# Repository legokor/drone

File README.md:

This repository houses all the essential project files for the drone project. It encompasses schematics, PCB designs, and firmwares.

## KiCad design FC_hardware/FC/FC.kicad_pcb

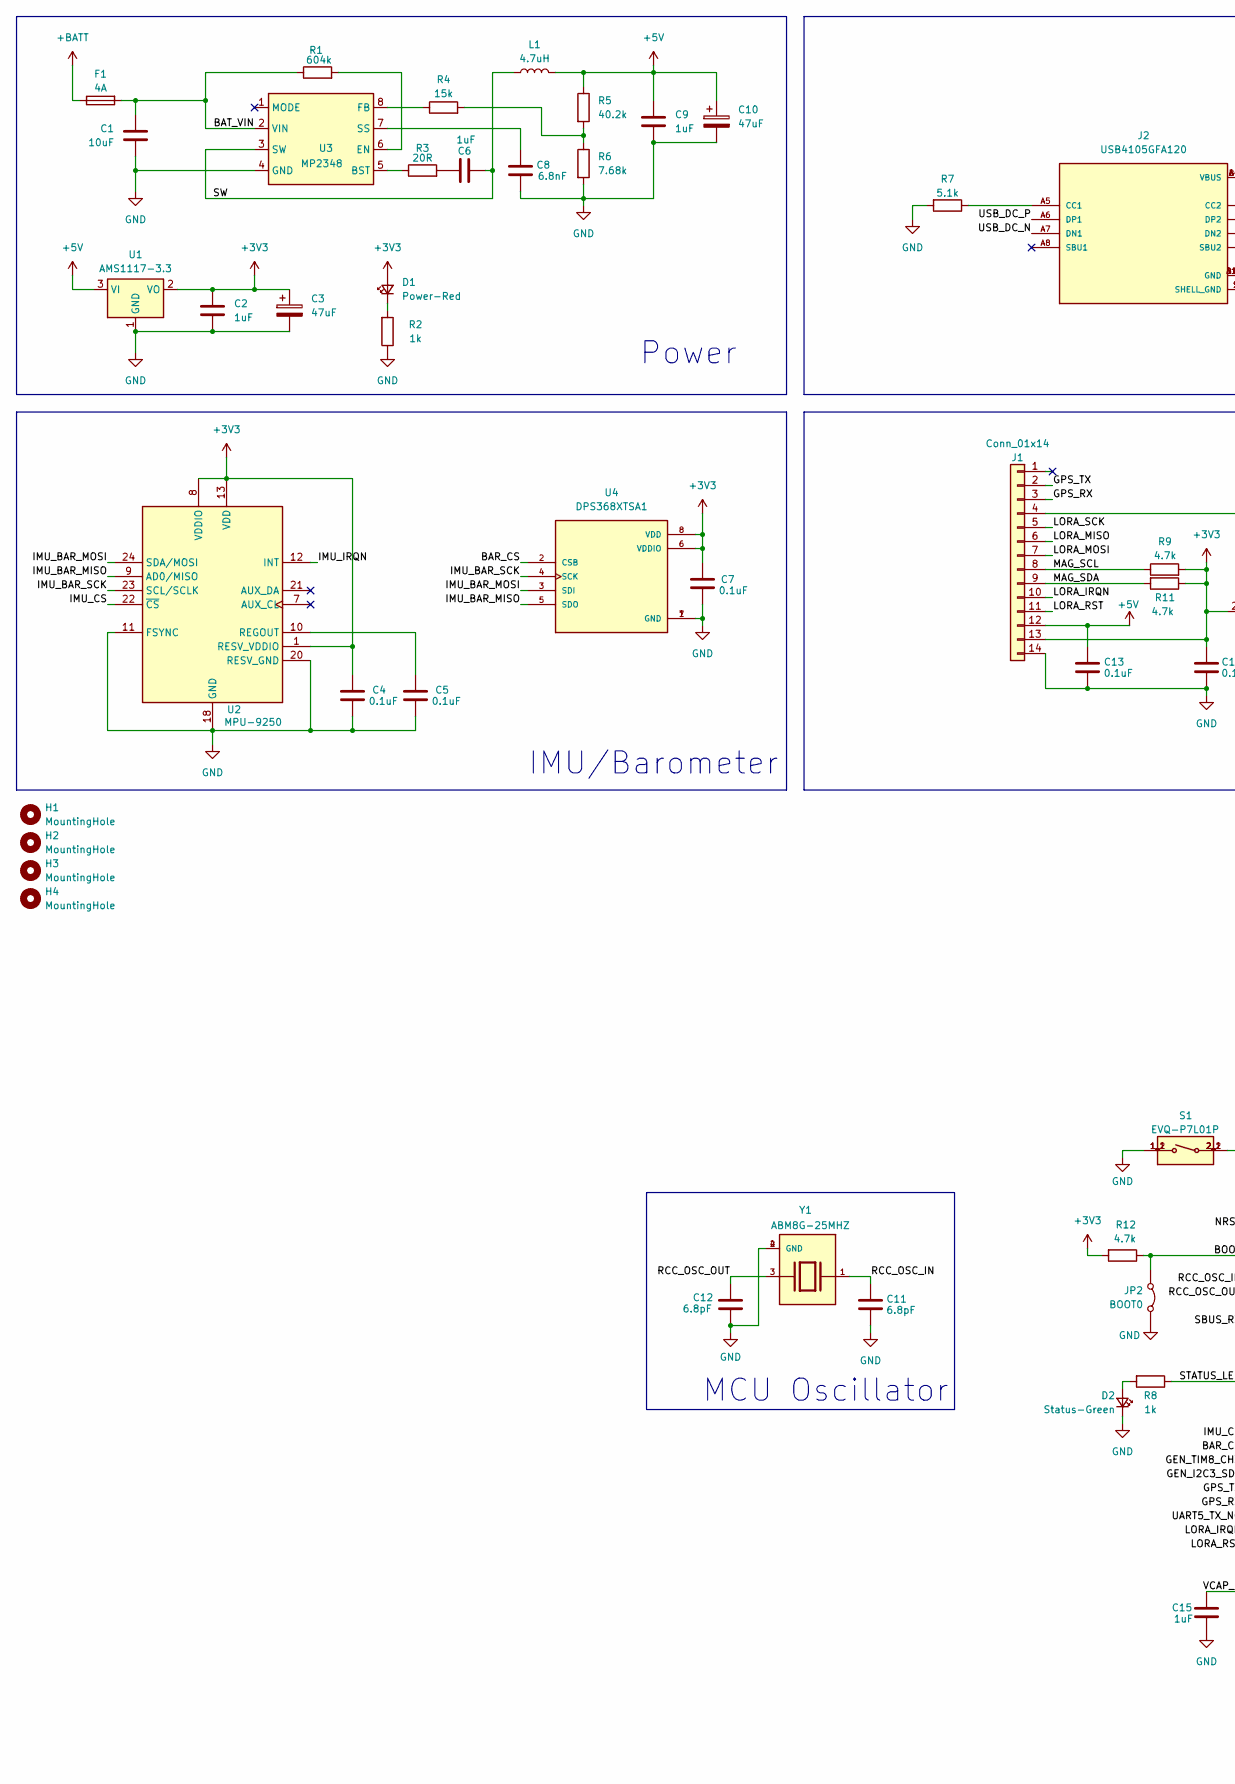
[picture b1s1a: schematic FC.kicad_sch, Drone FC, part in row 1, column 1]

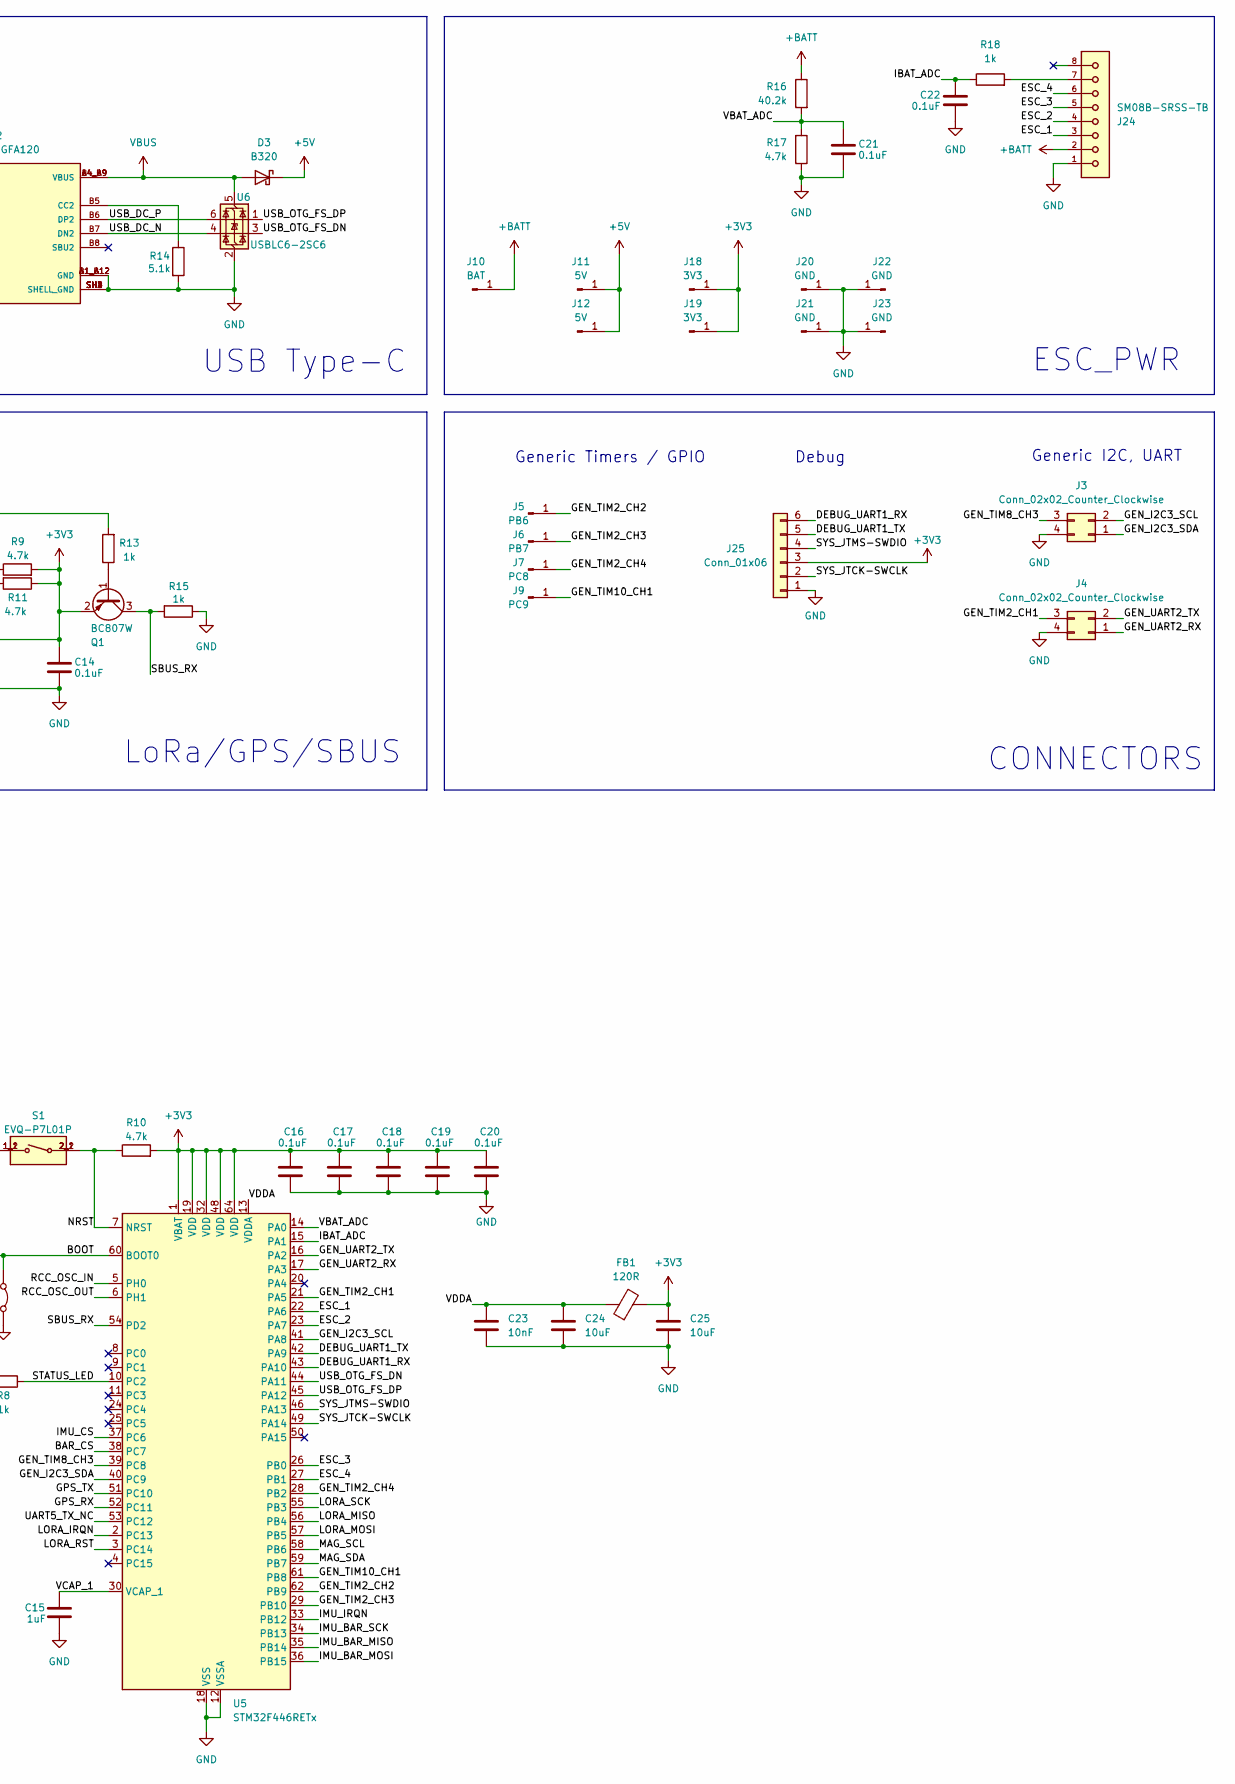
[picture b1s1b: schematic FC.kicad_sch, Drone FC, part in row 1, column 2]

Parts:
C1: 10uF; C_1206_3216Metric
C2, C6, C9, C15: 1uF; C_0805_2012Metric
C3, C10: 47uF; CP_EIA-3528-12_Kemet-T
C4, C5, C7, C13, C14, C16, C17, C18, C19, C20, C21, C22: 0.1uF; C_0603_1608Metric
C8: 6.8nF; C_0603_1608Metric
C11, C12: 6.8pF; C_0603_1608Metric
C23: 10nF; C_0603_1608Metric
C24, C25: 10uF; C_0603_1608Metric
D1: Power-Red; LED_0805_2012Metric
D2: Status-Green; LED_0805_2012Metric
D3: B320; D_SMA
F1: 4A; Fuse_0805_2012Metric
FB1: 120R; L_1206_3216Metric
H1, H2, H3, H4: MountingHole; MountingHole_3.2mm_M3
J1: Conn_01x14; JST_SH_SM14B-SRSS-TB_1x14-1MP_P1.00mm_Horizontal
J2: USB4105GFA120; GCT_USB4105GFA120; PARTREV B3
J3, J4: Conn_02x02_Counter_Clockwise; PinHeader_2x02_P1.27mm_Vertical
J5: PB6; 1.27mm_pin
J6: PB7; 1.27mm_pin
J7: PC8; 1.27mm_pin
J9: PC9; 1.27mm_pin
J10: BAT; PinHeader_1x01_P2.00mm_Vertical
J11, J12: 5V; 1.27mm_pin
J18, J19: 3V3; 1.27mm_pin
J20, J21, J22, J23: GND; 1.27mm_pin
J24: SM08B-SRSS-TB; JST_SH_SM08B-SRSS-TB_1x08-1MP_P1.00mm_Horizontal
J25: Conn_01x06; PinHeader_2x03_P1.27mm_Vertical
JP2: BOOT0; SolderJumper-2_P1.3mm_Bridged_RoundedPad1.0x1.5mm
L1: 4.7uH; L_Cenker_CKCS5040
Q1: BC807W; SOT-323_SC-70
R1: 604k; R_0603_1608Metric
R2, R8, R13, R15, R18: 1k; R_0603_1608Metric
R3: 20R; R_0603_1608Metric
R4: 15k; R_0603_1608Metric
R5, R16: 40.2k; R_0603_1608Metric
R6: 7.68k; R_0603_1608Metric
R7, R14: 5.1k; R_0603_1608Metric
R9, R10, R11, R12, R17: 4.7k; R_0603_1608Metric
S1: EVQ-P7L01P; SW_EVQ-P7L01P; PARTREV N/A
U1: AMS1117-3.3; SOT-223-3_TabPin2
U2: MPU-9250; InvenSense_QFN-24_3x3mm_P0.4mm
U3: MP2348; SOT-583-8
U4: DPS368XTSA1; XDCR_DPS368XTSA1
U5: STM32F446RETx; LQFP-64_10x10mm_P0.5mm
U6: USBLC6-2SC6; SOT-23-6
Y1: ABM8G-25MHZ; XTAL_ABM8G-25.000MHZ-4Y-T3; PARTREV 08.13.15

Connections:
+3V3: C2.1, C3.1, C4.1, C7.2, C14.1, C16.2, C17.2, C18.2, C19.2, C20.2, C25.2, D1.2 (A), FB1.2, J1.13, J18.1, J19.1, J25.3, Q1.2 (E), R9.2, R10.2, R11.1, R12.2, U1.2 (VO), U2.1 (RESV_VDDIO), U2.8 (VDDIO), U2.13 (VDD), U4.6 (VDDIO), U4.8 (VDD), U5.1 (VBAT), U5.19 (VDD), U5.32 (VDD), U5.48 (VDD), U5.64 (VDD)
+5V: C9.1, C10.1, C13.1, D3.1 (K), J1.12, J11.1, J12.1, L1.2, R5.1, U1.3 (VI)
+BATT: F1.1, J10.1, J24.2, R16.1
/BAR_CS: U4.2 (CSB), U5.38 (PC7)
/BAT_VIN: C1.1, F1.2, R1.1, U3.2 (VIN)
/BOOT: JP2.2 (B), R12.1, U5.60 (BOOT0)
/DEBUG_UART1_RX: J25.6, U5.43 (PA10)
/DEBUG_UART1_TX: J25.5, U5.42 (PA9)
/ESC_1: J24.3, U5.22 (PA6)
/ESC_2: J24.4, U5.23 (PA7)
/ESC_3: J24.5, U5.26 (PB0)
/ESC_4: J24.6, U5.27 (PB1)
/GEN_I2C3_SCL: J3.2, U5.41 (PA8)
/GEN_I2C3_SDA: J3.1, U5.40 (PC9)
/GEN_TIM2_CH1: J4.3, U5.21 (PA5)
/GEN_TIM2_CH2: J5.1, U5.62 (PB9)
/GEN_TIM2_CH3: J6.1, U5.29 (PB10)
/GEN_TIM2_CH4: J7.1, U5.28 (PB2)
/GEN_TIM8_CH3: J3.3, U5.39 (PC8)
/GEN_TIM10_CH1: J9.1, U5.61 (PB8)
/GEN_UART2_RX: J4.1, U5.17 (PA3)
/GEN_UART2_TX: J4.2, U5.16 (PA2)
/GPS_RX: J1.3, U5.52 (PC11)
/GPS_TX: J1.2, U5.51 (PC10)
/IBAT_ADC: C22.1, R18.1, U5.15 (PA1)
/IMU_BAR_MISO: U2.9 (AD0/MISO), U4.5 (SDO), U5.35 (PB14)
/IMU_BAR_MOSI: U2.24 (SDA/MOSI), U4.3 (SDI), U5.36 (PB15)
/IMU_BAR_SCK: U2.23 (SCL/SCLK), U4.4 (SCK), U5.34 (PB13)
/IMU_CS: U2.22 (~CS), U5.37 (PC6)
/IMU_IRQN: U2.12 (INT), U5.33 (PB12)
/LORA_IRQN: J1.10, U5.2 (PC13)
/LORA_MISO: J1.6, U5.56 (PB4)
/LORA_MOSI: J1.7, U5.57 (PB5)
/LORA_RST: J1.11, U5.3 (PC14)
/LORA_SCK: J1.5, U5.55 (PB3)
/MAG_SCL: J1.8, R9.1, U5.58 (PB6)
/MAG_SDA: J1.9, R11.2, U5.59 (PB7)
/NRST: R10.1, S1.2_1, S1.2_2, U5.7 (NRST)
/RCC_OSC_IN: C11.2, U5.5 (PH0), Y1.1
/RCC_OSC_OUT: C12.1, U5.6 (PH1), Y1.3
/SBUS_RX: Q1.3 (C), R15.2, U5.54 (PD2)
/STATUS_LED: R8.1, U5.10 (PC2)
/SW: C6.2, L1.1, U3.3 (SW)
/SYS_JTCK-SWCLK: J25.2, U5.49 (PA14)
/SYS_JTMS-SWDIO: J25.4, U5.46 (PA13)
/UART5_TX_NC: U5.53 (PC12)
/USB_DC_N: J2.A7 (DN1), J2.B7 (DN2), U6.4 (I/O2)
/USB_DC_P: J2.A6 (DP1), J2.B6 (DP2), U6.6 (I/O1)
/USB_OTG_FS_DN: U5.44 (PA11), U6.3 (I/O2)
/USB_OTG_FS_DP: U5.45 (PA12), U6.1 (I/O1)
/VBAT_ADC: C21.1, R16.2, R17.2, U5.14 (PA0)
/VCAP_1: C15.2, U5.30 (VCAP_1)
/VDDA: C23.2, C24.2, FB1.1, U5.13 (VDDA)
GND: C1.2, C2.2, C3.2, C4.2, C5.2, C7.1, C8.2, C9.2, C10.2, C11.1, C12.2, C13.2, C14.2, C15.1, C16.1, C17.1, C18.1, C19.1, C20.1, C21.2, C22.2, C23.1, C24.1, C25.1, D2.1 (K), J1.14, J2.A1_B12 (GND), J2.B1_A12 (GND), J2.SH1 (SHELL_GND), J2.SH2 (SHELL_GND), J2.SH3 (SHELL_GND), J2.SH4 (SHELL_GND), J3.4, J4.4, J20.1, J21.1, J22.1, J23.1, J24.1, J25.1, JP2.1 (A), R2.1, R6.2, R7.2, R14.2, R15.1, R17.1, S1.1_1, S1.1_2, U1.1 (GND), U2.11 (FSYNC), U2.18 (GND), U2.20 (RESV_GND), U3.4 (GND), U4.1 (GND), U4.7 (GND), U5.12 (VSSA), U5.18 (VSS), U5.31 (VSS), U5.47 (VSS), U5.63 (VSS), U6.2 (GND), Y1.2 (GND), Y1.4 (GND)
unnamed: C6.1, R3.2
unnamed: D1.1 (K), R2.2
unnamed: D2.2 (A), R8.2
unnamed: J1.4, R13.2
unnamed: J2.A5 (CC1), R7.1
unnamed: J2.B5 (CC2), R14.1
unnamed: J24.7, R18.2
unnamed: Q1.1 (B), R13.1
unnamed: R4.2, R5.2, R6.1
unnamed: C5.1, U2.10 (REGOUT)
unnamed: R3.1, U3.5 (BST)
unnamed: R1.2, U3.6 (EN)
unnamed: R4.1, U3.8 (FB)
unnamed: C8.1, U3.7 (SS)
VBUS: D3.2 (A), J2.A4_B9 (VBUS), J2.B4_A9 (VBUS), U6.5 (VBUS)

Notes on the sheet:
IMU/Barometer
Generic Timers / GPIO
Debug
USB Type-C
Power
Generic I2C, UART
ESC_PWR
MCU Oscillator
LoRa/GPS/SBUS
CONNECTORS

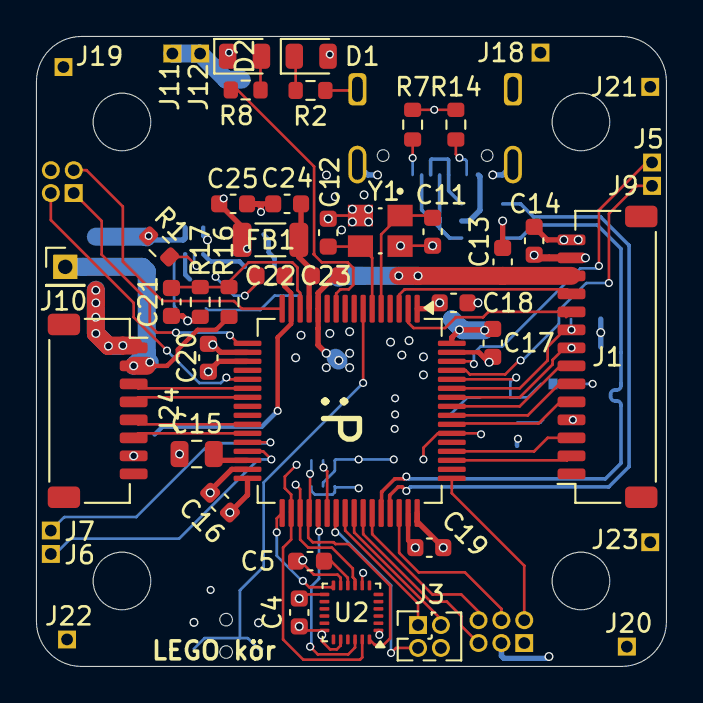
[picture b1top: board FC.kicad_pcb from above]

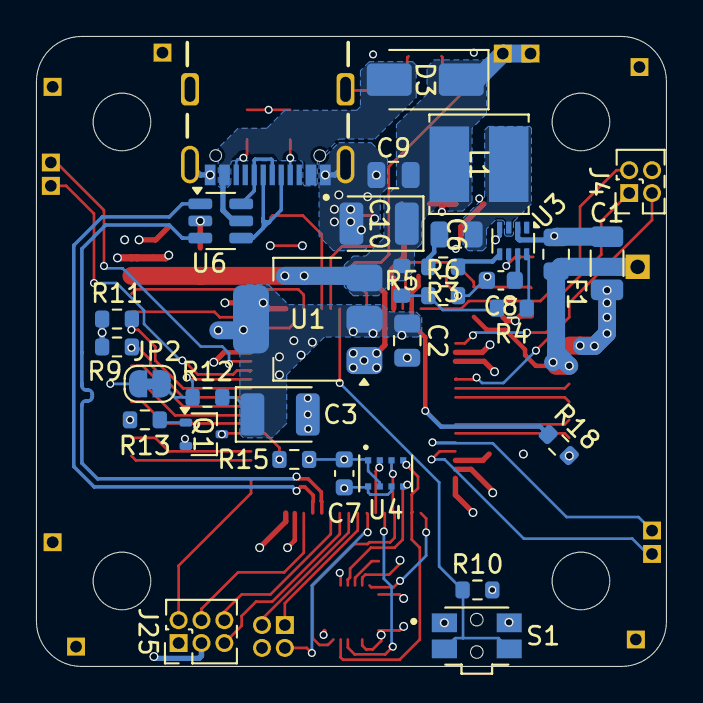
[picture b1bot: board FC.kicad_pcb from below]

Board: 4 copper layers, 35.0 x 35.0 mm, 82 parts (32 on the bottom side), 68 nets.

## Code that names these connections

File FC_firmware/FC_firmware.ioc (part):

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Mcu.Name=STM32F446R(C-E)Tx
Mcu.Package=LQFP64
Mcu.UserName=STM32F446RETx
PA0-WKUP.GPIOParameters=GPIO_Label
PA0-WKUP.GPIO_Label=VBAT_ADC
PA0-WKUP.Signal=ADCx_IN0
PA1.GPIOParameters=GPIO_Label
PA1.GPIO_Label=IBAT_ADC
PA1.Signal=ADCx_IN1
PA10.GPIOParameters=GPIO_Label
PA10.GPIO_Label=DEBUG_UART1_RX
PA10.Mode=Asynchronous
PA10.Signal=USART1_RX
PA11.Mode=Device_Only
PA11.Signal=USB_OTG_FS_DM
PA12.Mode=Device_Only
PA12.Signal=USB_OTG_FS_DP
PA13.Mode=Serial_Wire
PA13.Signal=SYS_JTMS-SWDIO
PA14.Mode=Serial_Wire
PA14.Signal=SYS_JTCK-SWCLK
PA2.GPIOParameters=GPIO_Label
PA2.GPIO_Label=GEN_UART2_TX
PA2.Mode=Asynchronous
PA2.Signal=USART2_TX
PA3.GPIOParameters=GPIO_Label
PA3.GPIO_Label=GEN_UART2_RX
PA3.Mode=Asynchronous
PA3.Signal=USART2_RX
PA5.GPIOParameters=GPIO_Label
PA5.GPIO_Label=GEN_TIM2_CH1
PA5.Signal=S_TIM2_CH1_ETR
PA6.GPIOParameters=GPIO_Label
PA6.GPIO_Label=ESC_1
PA6.Signal=S_TIM3_CH1
PA7.GPIOParameters=GPIO_Label
PA7.GPIO_Label=ESC_2
PA7.Signal=S_TIM3_CH2
PA8.GPIOParameters=GPIO_Label
PA8.GPIO_Label=GEN_I2C3_SCL
PA8.Mode=I2C
PA8.Signal=I2C3_SCL
PA9.GPIOParameters=GPIO_Label
PA9.GPIO_Label=DEBUG_UART1_TX
PA9.Mode=Asynchronous
PA9.Signal=USART1_TX
PB0.GPIOParameters=GPIO_Label
PB0.GPIO_Label=ESC_3
PB0.Signal=S_TIM3_CH3
PB1.GPIOParameters=GPIO_Label
PB1.GPIO_Label=ESC_4
PB1.Signal=S_TIM3_CH4
PB10.GPIOParameters=GPIO_Label
PB10.GPIO_Label=GEN_TIM2_CH3
PB10.Signal=S_TIM2_CH3
PB12.GPIOParameters=GPIO_Label
PB12.GPIO_Label=IMU_IRQN
PB12.Signal=GPXTI12
PB13.GPIOParameters=GPIO_Label
PB13.GPIO_Label=IMU_BAR_SCK
PB13.Mode=Full_Duplex_Master
PB13.Signal=SPI2_SCK
PB14.GPIOParameters=GPIO_Label
PB14.GPIO_Label=IMU_BAR_MISO
PB14.Mode=Full_Duplex_Master
PB14.Signal=SPI2_MISO
PB15.GPIOParameters=GPIO_Label
PB15.GPIO_Label=IMU_BAR_MOSI
PB15.Mode=Full_Duplex_Master
PB15.Signal=SPI2_MOSI
PB2.GPIOParameters=GPIO_Label
PB2.GPIO_Label=GEN_TIM2_CH4
PB2.Signal=S_TIM2_CH4
PB3.GPIOParameters=GPIO_Label
PB3.GPIO_Label=LORA_SCK
PB3.Mode=Full_Duplex_Master
PB3.Signal=SPI1_SCK
PB4.GPIOParameters=GPIO_Label
PB4.GPIO_Label=LORA_MISO
PB4.Mode=Full_Duplex_Master
PB4.Signal=SPI1_MISO
PB5.GPIOParameters=GPIO_Label
PB5.GPIO_Label=LORA_MOSI
PB5.Mode=Full_Duplex_Master
PB5.Signal=SPI1_MOSI
PB6.GPIOParameters=GPIO_Label
PB6.GPIO_Label=MAG_SCL
PB6.Mode=I2C
PB6.Signal=I2C1_SCL
PB7.GPIOParameters=GPIO_Label
PB7.GPIO_Label=MAG_SDA
PB7.Mode=I2C
PB7.Signal=I2C1_SDA
PB8.GPIOParameters=GPIO_Label
PB8.GPIO_Label=GEN_TIM10_CH1
PB8.Signal=S_TIM10_CH1
PB9.GPIOParameters=GPIO_Label
PB9.GPIO_Label=GEN_TIM2_CH2
PB9.Signal=S_TIM2_CH2
PC10.GPIOParameters=GPIO_Label
PC10.GPIO_Label=GPS_TX
PC10.Mode=Asynchronous
PC10.Signal=UART4_TX
PC11.GPIOParameters=GPIO_Label
PC11.GPIO_Label=GPS_RX
PC11.Mode=Asynchronous
PC11.Signal=UART4_RX
PC12.GPIOParameters=GPIO_Label
PC12.GPIO_Label=UART5_TX_NC
PC12.Mode=Asynchronous
PC12.Signal=UART5_TX
PC13.GPIOParameters=GPIO_Label
PC13.GPIO_Label=LORA_IRQN
PC13.Signal=GPXTI13
PC14-OSC32_IN.GPIOParameters=GPIO_Label
PC14-OSC32_IN.GPIO_Label=LORA_RST
PC14-OSC32_IN.Signal=GPIO_Output
PC2.GPIOParameters=GPIO_Label
PC2.GPIO_Label=STATUS_LED
PC2.Signal=GPIO_Output
PC6.GPIOParameters=GPIO_Label
PC6.GPIO_Label=IMU_CS
PC6.Signal=GPIO_Output
PC7.GPIOParameters=GPIO_Label
PC7.GPIO_Label=BAR_CS
PC7.Signal=GPIO_Output
PC8.GPIOParameters=GPIO_Label
PC8.GPIO_Label=GEN_TIM8_CH3
PC8.Signal=S_TIM8_CH3
PC9.GPIOParameters=GPIO_Label
PC9.GPIO_Label=GEN_I2C3_SDA
PC9.Mode=I2C
PC9.Signal=I2C3_SDA
PD2.GPIOParameters=GPIO_Label
PD2.GPIO_Label=SBUS_RX
PD2.Mode=Asynchronous
PD2.Signal=UART5_RX
PH0-OSC_IN.Mode=HSE-External-Oscillator
PH0-OSC_IN.Signal=RCC_OSC_IN
PH1-OSC_OUT.Mode=HSE-External-Oscillator
PH1-OSC_OUT.Signal=RCC_OSC_OUT
RCC.SYSCLKFreq_VALUE=168333333.33333334
RCC.SYSCLKSource=RCC_SYSCLKSOURCE_PLLCLK
board=custom

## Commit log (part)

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2024-09-01 Power section complete
2024-09-11 STM pin config added
2024-09-13 schematic things...
2024-09-15 schematic is done
2024-09-15 PCB DRC and outline
2024-09-18 footprint and PCB outline changes
2024-09-21 Layout pcb
2024-09-21 Round corners, fix some DRC violations
2024-09-22 Fix some via and silkscreen issues
2024-09-22 0201 changed to 0603
2024-09-22 fixup! 0201 changed to 0603
2024-09-28 Pin config changed, LoRa module removed from board
2024-10-04 Improve schematic, settings
2024-10-04 Add gerbers to gitignore
2024-10-04 Board outline, DRU
2024-10-16 stm pin config updated, TODO: schematic update
2024-10-23 Update stm pin config, clean up schematic
2024-11-08 Dump pcb design
2024-11-11 min via hole d enlarged to 0.3mm and all vias resized accordingly
2024-11-13 Finalize design
2024-11-21 Add style guide and format config
2024-11-21 Add high-level software architecture plan
2024-11-27 farnell BOM
2024-11-27 Improve modules.png
2024-11-28 Add module generator script
    A bit overengineered, I know...
2024-11-28 Generate driver modules
2024-11-28 Generate software modules
2024-11-28 Call management entry from main.c
2024-11-28 Migrate mx project
2024-12-08 Start working on telemetry board
2024-12-08 Rename megmt module to sys
2024-12-08 Start working on log and tel modules
2024-12-11 Set chip antenna footprint
2024-12-18 Clean up
2025-02-05 Use jinja templates for codegen
2025-02-06 Dump experimentations
2025-02-06 Add utils to gen
2025-02-07 Fix includes in gen
2025-02-07 Add .vscode to gitignore
2025-02-10 Remove hardcoded spi refs from bar driver
2025-03-19 Setup cmake
2025-03-19 Fix whitespace issue in header template
2025-03-21 Add readme for build instructions
2025-03-21 Add CMSIS DSP as a git submodule
2025-04-03 Convert to raw binary using cmake
2025-04-03 Add link-time optimizations to release build
2025-04-03 Make CMSIS-DSP a shallow submodule
2025-04-03 Fix lto
2025-04-22 act.h,act.c
2025-04-26 Add instructions for CubeIDE / Windows
2025-04-30 Add register generator script
2025-04-30 Remove old guide header
2025-04-30 Format main.c
2025-04-30 Fix tel (for now)
2025-04-30 Generate bar registers
2025-04-30 Update sys
2025-04-30 Refactor act
2025-05-03 minor fixes, temporary module removal
2025-05-03 UART, IMU and INT modules
2025-05-03 functional IMU test code
2025-05-03 esc test
2025-05-03 sbus rc receiver driver working impl
2025-05-03 rc driver initial impl
2025-05-03 fixes and barometer test code
2025-05-03 code gen fix
2025-05-07 Add disarm mechanism
2025-05-07 Start working on descriptions of modules
2025-05-07 Remove timer init code
    Will be generated by MX
2025-05-14 Document high-level modes
2025-05-14 Review imu, rc, uart
    Fix buffering in rc + code style changes to imu and uart.
2025-05-14 Build error...
2025-05-14 fixes
2025-05-21 Add modes
2025-05-22 Generate bar regs
2025-05-22 Fix naming, minor refactors
2025-05-25 Fix build errors
2025-06-06 Add err module
2025-06-06 Minor refactor
2025-06-06 Telemetry now writes messages, not bytes
2025-06-06 Make _act_armed volatile
    Also refactored a bit.
2025-06-06 Use err, add some asserts (MORE ARE NEEDED!!!)
2025-06-19 Add clangd cache to gitignore
2025-06-19 Only assert in debug
2025-06-19 Nodiscard
2025-06-19 Clean up / add includes
2025-06-19 Refactor log.c
2025-06-19 Fix interrupt naming
2025-06-19 Add sys_initalized(), sys_abort()
2025-06-19 Fix building CMSIS-DSP
2025-06-19 Remove CMSIS-DSP submodule in favor of CMake FetchContent
2025-06-19 Add HAL dma sources to cmake
2025-06-19 Fix warnings
2025-06-19 Fix linker warnings
2025-06-19 Add err.c to CMakeLists
2025-06-19 Update build instructions
2025-06-19 Fix arm gcc download link
2025-06-25 Simplify Windows action setup
2025-06-25 Use winget on windows-2025
2025-06-25 Install less stuff
2025-06-25 Use another action to install gcc
2025-06-25 Create build action
2025-06-25 Don't build release on windows
2025-09-19 Gitignore only build/
2025-09-19 Add float printf support, link-time optimalization
2025-09-19 Add interrup handlers to Core
2025-09-19 Add loop-based parsing for SBUS
2025-09-19 Refactor, add more error handling to imu driver
2025-09-19 Make llc and act compatible
2025-09-19 Refactor irq
2025-09-19 Add some utils
2025-09-19 Remove duplicated startup asm file
2025-09-19 Improve err module
2025-09-19 Dump new sys.c
2025-09-19 Add some error handling to tel
2025-09-19 Clean up log
2025-09-19 Sketch out guide
2025-09-19 Add disarm logic to ctrl
2025-09-19 Add basic dsp
2025-09-19 Fix typo in uart
2025-09-26 Refactor rc
2025-09-26 Use more cmsis in dsp
2025-09-26 Add noreturn hint to fatal errors
2025-09-26 Implement llc
2025-09-26 Roughly implement guide
2025-09-26 Log refactors, sys printing
2025-10-02 Error handling
2025-11-05 Rc works!!!
2025-12-03 Full stack integrated, arm/disarm works
2025-12-03 Fix ci?
2025-12-10 log logic fixes
2026-03-10 Minor fixes, add ADC module
2026-03-10 Fix build action trigger paths
2026-03-11 Works...
2026-03-18 Update HAL version, modify adc settings with MX, generate
2026-03-18 Battery threshold
2026-03-18 IMU bugfix
2026-03-18 Fix voltage stuff
2026-03-19 Use DMA to make ADC completely automatic
2026-05-08 Add averaging to dsp
2026-05-09 Implemented rotation correction
2026-06-03 Constanly keep PWM at 0
2026-06-11 IMU fix?
2026-06-11 Make disarmed pwm toggleable
2026-06-11 dsp fix?
2026-06-11 sys: reorder init seq, improve logging
2026-06-17 Update act to be modular, add dshot driver
2026-06-17 save
2026-06-18 IMU working
2026-06-18 Fix act
2026-06-18 dshot debug 1
2026-06-18 Revert to pwm
2026-06-24 dshot workie
2026-06-25 working together with imu now
2026-06-25 Fix telemetry logging channel names
